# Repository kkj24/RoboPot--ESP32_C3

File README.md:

PCB Design for ESP32-C3-SuperMini

This File Directory for PlatformIO Extension

You can also open the Local Web Dashboard for the RoboPot Dashboard
The URL for the dashboard is  http://robopot.local

schematic preview design

Wiring preview design

The PCB design was created in the KiCad platform. You can ask me to give Gerber file PCBs

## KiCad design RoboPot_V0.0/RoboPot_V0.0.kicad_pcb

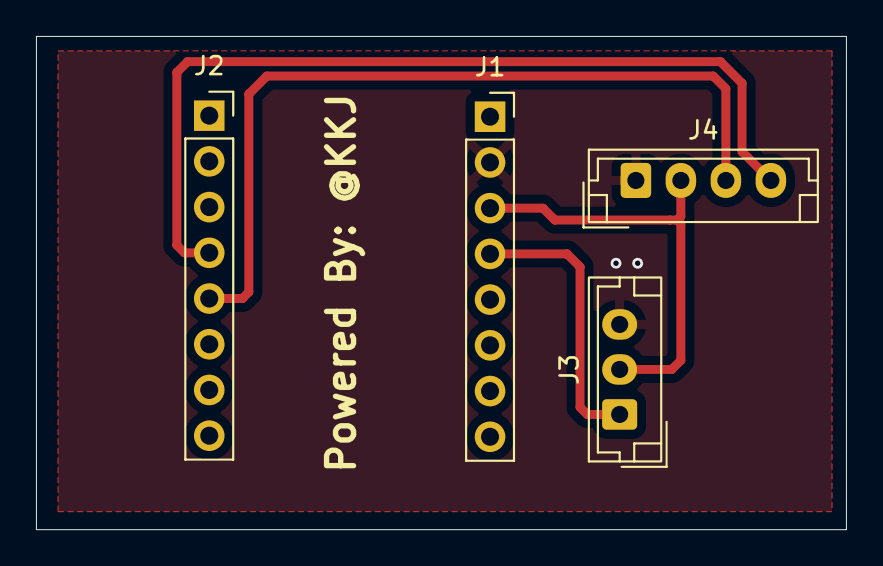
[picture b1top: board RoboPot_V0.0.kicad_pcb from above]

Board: 2 copper layers, 45.0 x 27.4 mm, 4 parts (0 on the bottom side), 5 nets.

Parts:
J1, J2: Conn_01x08_Socket; PinSocket_1x08_P2.54mm_Vertical
J3: Conn_01x03_Pin; JST_EH_B3B-EH-A_1x03_P2.50mm_Vertical
J4: Conn_01x04_Pin; JST_EH_B4B-EH-A_1x04_P2.50mm_Vertical

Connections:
+3.3V: J1.3 (3V3), J3.2 (VCC), J4.2 (VCC)
GND: J1.2 (GND), J3.3 (GND), J4.1 (GND)
OUT: J1.4, J3.1 (OUT)
SCL: J2.5 (9), J4.3 (SCL)
SDA: J2.4 (8), J4.4 (SDA)

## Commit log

2026-05-22 fist commit
2026-05-22 PCB_Design
